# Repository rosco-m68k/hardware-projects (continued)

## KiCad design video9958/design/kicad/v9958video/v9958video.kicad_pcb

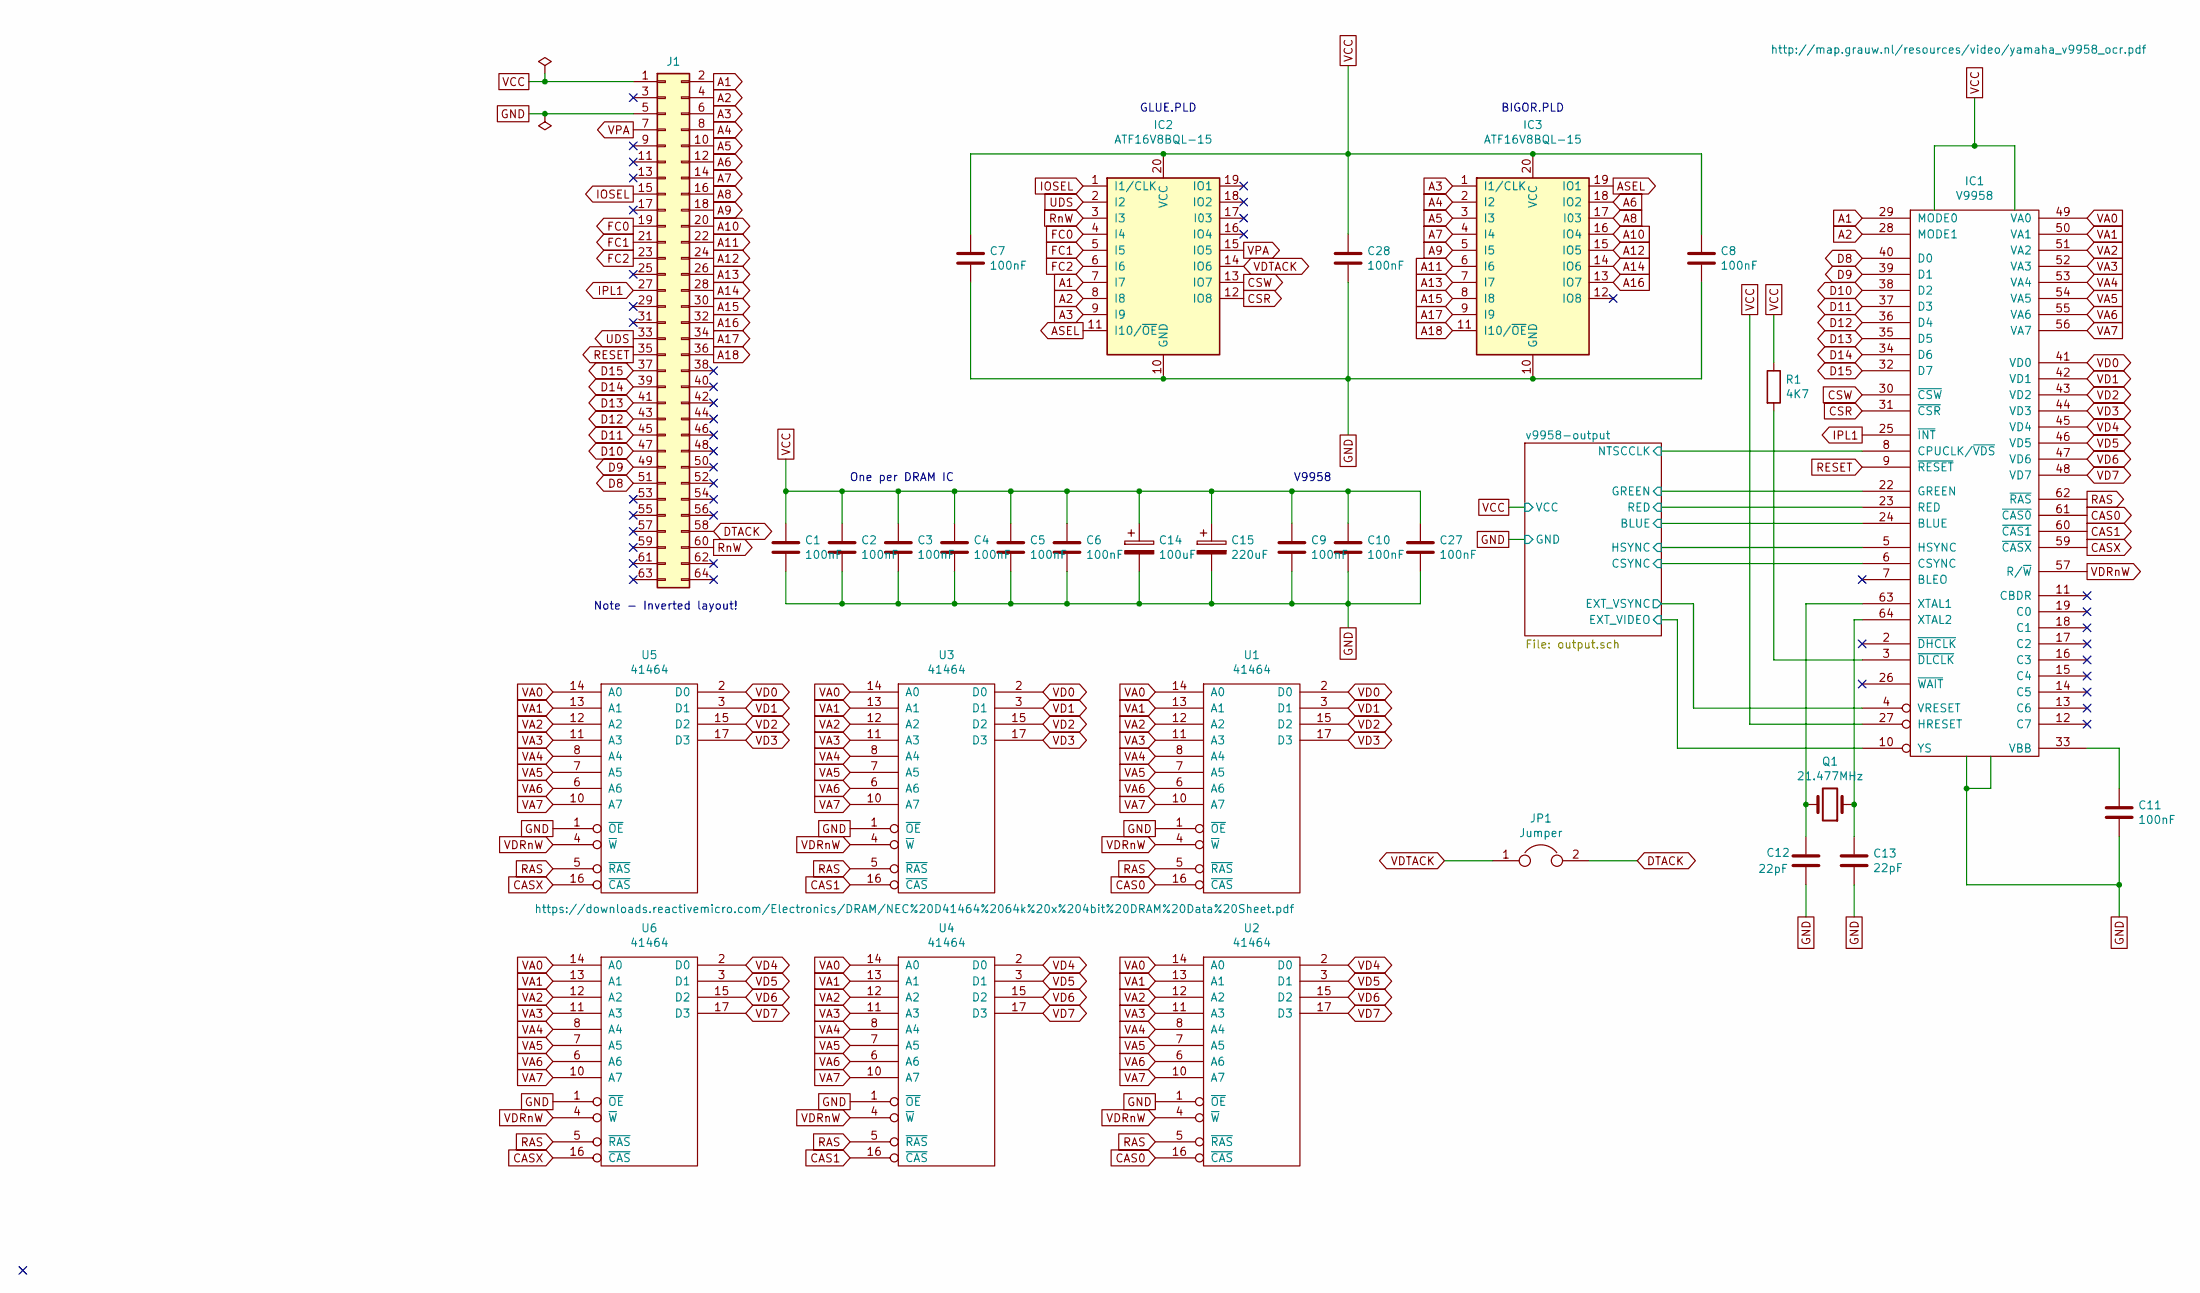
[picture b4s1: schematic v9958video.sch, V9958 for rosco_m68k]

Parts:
C1, C2, C3, C4, C5, C6, C7, C8, C9, C10, C11, C27, C28: 100nF; C_Rect_L7.0mm_W2.5mm_P5.00mm
C12, C13: 22pF; C_Rect_L7.0mm_W2.5mm_P5.00mm
C14: 100uF; CP_Radial_D5.0mm_P2.50mm
C15: 220uF; CP_Radial_D6.3mm_P2.50mm
IC1: V9958; sdip64
IC2, IC3: ATF16V8BQL-15; DIP-20_W7.62mm_LongPads
J1: Conn_02x32_Odd_Even; pin-2X32
JP1: Jumper; pin-1X02
Q1: 21.477MHz; HC49_S
R1: 4K7; R-0207_10
U1, U2, U3, U4, U5, U6: 41464; DIP-18_W7.62mm_Socket_LongPads

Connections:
/v9958-output/BLUE: IC1.24 (BLUE); also elsewhere on the board
/v9958-output/CSYNC: IC1.6 (CSYNC); also elsewhere on the board
/v9958-output/EXT_VIDEO: IC1.10 (YS); also elsewhere on the board
/v9958-output/EXT_VSYNC: IC1.4 (VRESET); also elsewhere on the board
/v9958-output/GREEN: IC1.22 (GREEN); also elsewhere on the board
/v9958-output/HSYNC: IC1.5 (HSYNC); also elsewhere on the board
/v9958-output/NTSCCLK: IC1.8 (CPUCLK/~VDS); also elsewhere on the board
/v9958-output/RED: IC1.23 (RED); also elsewhere on the board
A1: IC1.29 (MODE0), IC2.7 (I7), J1.2
A2: IC1.28 (MODE1), IC2.8 (I8), J1.4
A3: IC2.9 (I9), IC3.1 (I1/CLK), J1.6
A4: IC3.2 (I2), J1.8
A5: IC3.3 (I3), J1.10
A6: IC3.18 (IO2), J1.12
A7: IC3.4 (I4), J1.14
A8: IC3.17 (I03), J1.16
A9: IC3.5 (I5), J1.18
A10: IC3.16 (IO4), J1.20
A11: IC3.6 (I6), J1.22
A12: IC3.15 (IO5), J1.24
A13: IC3.7 (I7), J1.26
A14: IC3.14 (IO6), J1.28
A15: IC3.8 (I8), J1.30
A16: IC3.13 (IO7), J1.32
A17: IC3.9 (I9), J1.34
A18: IC3.11 (I10/~OE~), J1.36
ASEL: IC2.11 (I10/~OE~), IC3.19 (IO1)
CAS0: IC1.61 (~CAS0), U1.16 (~CAS), U2.16 (~CAS)
CAS1: IC1.60 (~CAS1), U3.16 (~CAS), U4.16 (~CAS)
CASX: IC1.59 (~CASX), U5.16 (~CAS), U6.16 (~CAS)
CSR: IC1.31 (~CSR), IC2.12 (IO8)
CSW: IC1.30 (~CSW), IC2.13 (IO7)
D8: IC1.40 (D0), J1.51
D9: IC1.39 (D1), J1.49
D10: IC1.38 (D2), J1.47
D11: IC1.37 (D3), J1.45
D12: IC1.36 (D4), J1.43
D13: IC1.35 (D5), J1.41
D14: IC1.34 (D6), J1.39
D15: IC1.32 (D7), J1.37
DTACK: J1.58, JP1.2
FC0: IC2.4 (I4), J1.19
FC1: IC2.5 (I5), J1.21
FC2: IC2.6 (I6), J1.23
IOSEL: IC2.1 (I1/CLK), J1.15
IPL1: IC1.25 (~INT), J1.27
unnamed: C11.1, IC1.33 (VBB)
unnamed: C12.1, IC1.63 (XTAL1), Q1.2
unnamed: C13.1, IC1.64 (XTAL2), Q1.1
unnamed: IC1.3 (~DLCLK), R1.2
RAS: IC1.62 (~RAS), U1.5 (~RAS), U2.5 (~RAS), U3.5 (~RAS), U4.5 (~RAS), U5.5 (~RAS), U6.5 (~RAS)
RESET: IC1.9 (~RESET), J1.35
RnW: IC2.3 (I3), J1.60
UDS: IC2.2 (I2), J1.33
VA0: IC1.49 (VA0), U1.14 (A0), U2.14 (A0), U3.14 (A0), U4.14 (A0), U5.14 (A0), U6.14 (A0)
VA1: IC1.50 (VA1), U1.13 (A1), U2.13 (A1), U3.13 (A1), U4.13 (A1), U5.13 (A1), U6.13 (A1)
VA2: IC1.51 (VA2), U1.12 (A2), U2.12 (A2), U3.12 (A2), U4.12 (A2), U5.12 (A2), U6.12 (A2)
VA3: IC1.52 (VA3), U1.11 (A3), U2.11 (A3), U3.11 (A3), U4.11 (A3), U5.11 (A3), U6.11 (A3)
VA4: IC1.53 (VA4), U1.8 (A4), U2.8 (A4), U3.8 (A4), U4.8 (A4), U5.8 (A4), U6.8 (A4)
VA5: IC1.54 (VA5), U1.7 (A5), U2.7 (A5), U3.7 (A5), U4.7 (A5), U5.7 (A5), U6.7 (A5)
VA6: IC1.55 (VA6), U1.6 (A6), U2.6 (A6), U3.6 (A6), U4.6 (A6), U5.6 (A6), U6.6 (A6)
VA7: IC1.56 (VA7), U1.10 (A7), U2.10 (A7), U3.10 (A7), U4.10 (A7), U5.10 (A7), U6.10 (A7)
VD0: IC1.41 (VD0), U1.2 (D0), U3.2 (D0), U5.2 (D0)
VD1: IC1.42 (VD1), U1.3 (D1), U3.3 (D1), U5.3 (D1)
VD2: IC1.43 (VD2), U1.15 (D2), U3.15 (D2), U5.15 (D2)
VD3: IC1.44 (VD3), U1.17 (D3), U3.17 (D3), U5.17 (D3)
VD4: IC1.45 (VD4), U2.2 (D0), U4.2 (D0), U6.2 (D0)
VD5: IC1.46 (VD5), U2.3 (D1), U4.3 (D1), U6.3 (D1)
VD6: IC1.47 (VD6), U2.15 (D2), U4.15 (D2), U6.15 (D2)
VD7: IC1.48 (VD7), U2.17 (D3), U4.17 (D3), U6.17 (D3)
VDRnW: IC1.57 (R/~W), U1.4 (~W), U2.4 (~W), U3.4 (~W), U4.4 (~W), U5.4 (~W), U6.4 (~W)
VDTACK: IC2.14 (IO6), JP1.1
VPA: IC2.15 (IO5), J1.7

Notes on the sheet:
GLUE.PLD
BIGOR.PLD
Note - Inverted layout!
One per DRAM IC
V9958

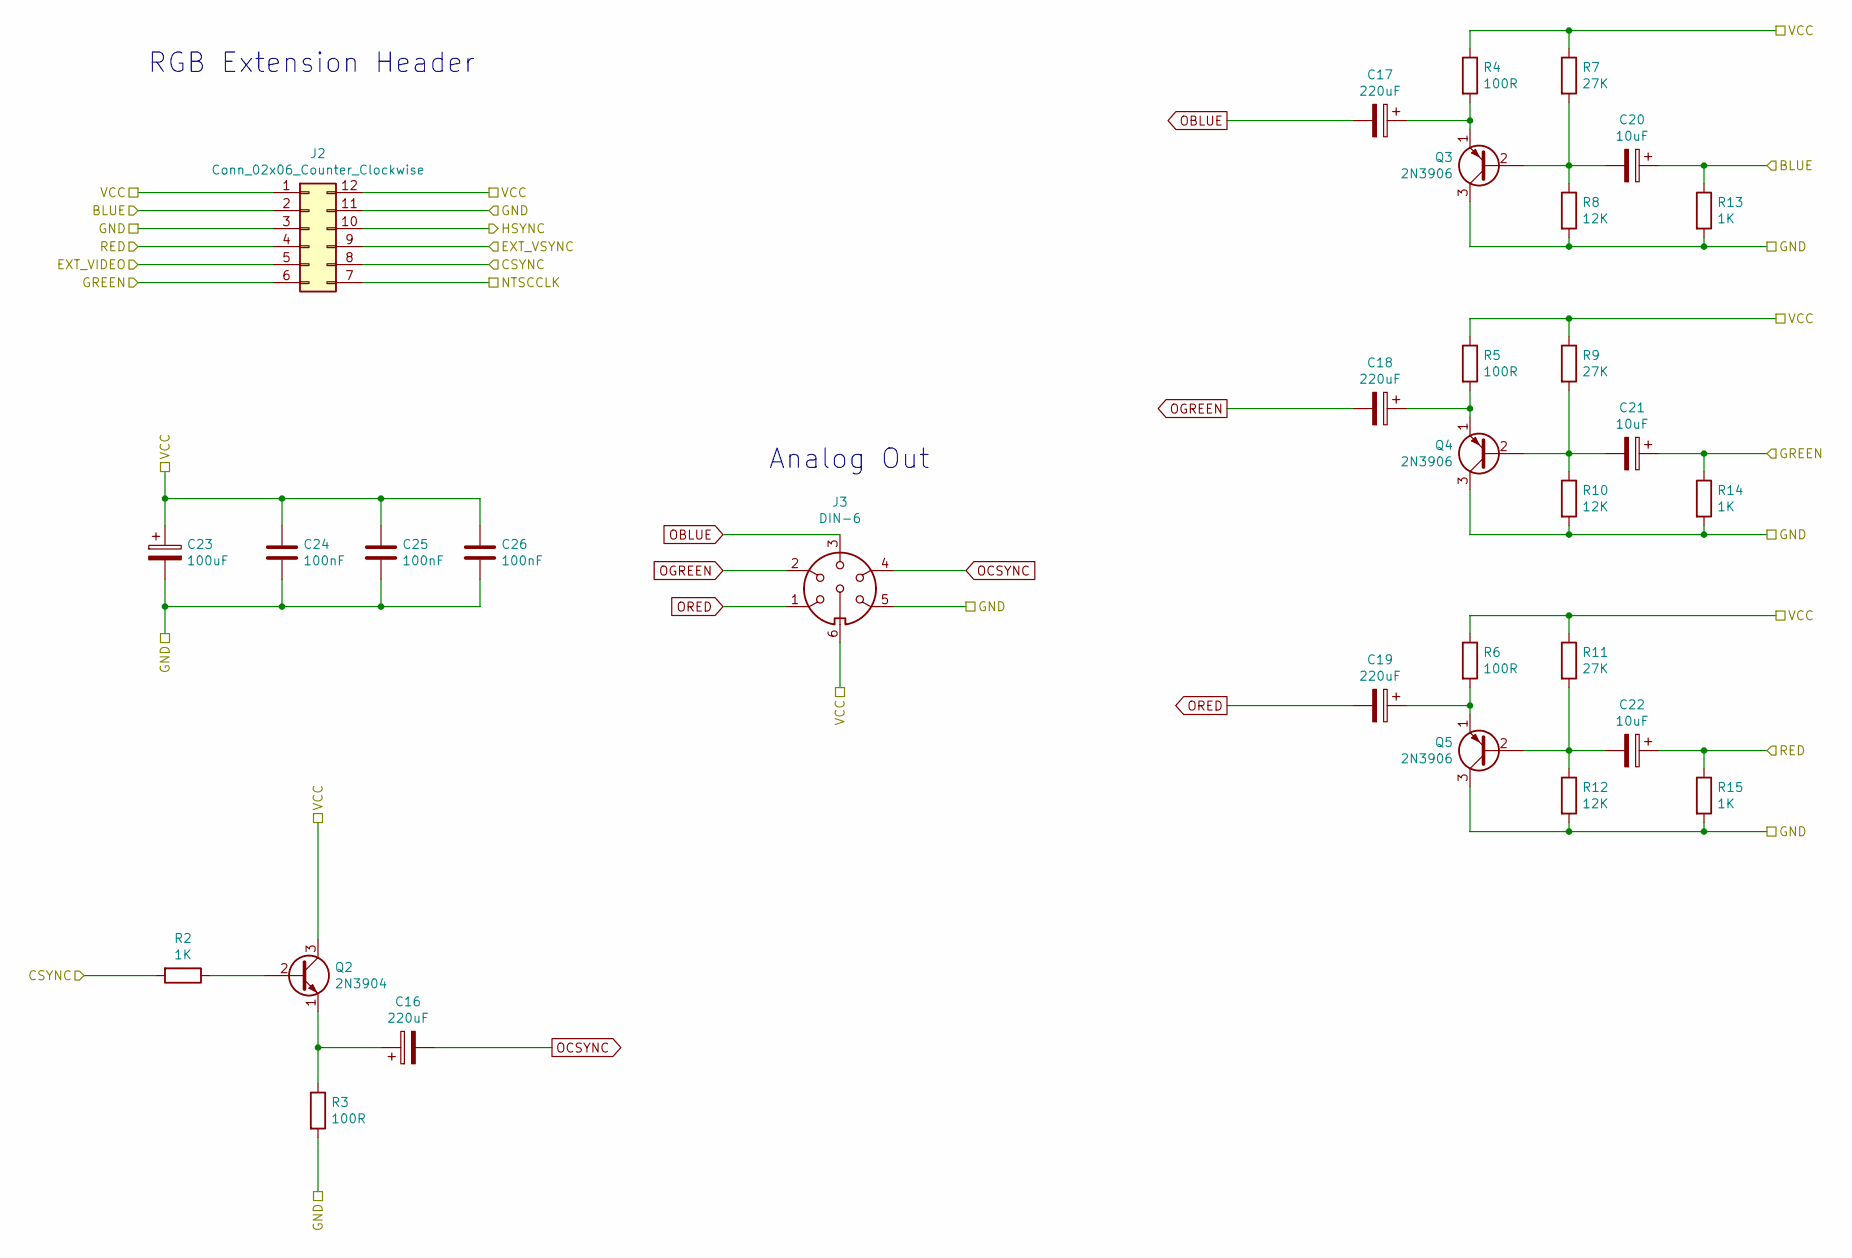
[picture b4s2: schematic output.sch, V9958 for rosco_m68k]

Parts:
C16, C17, C18, C19: 220uF; CP_Radial_D6.3mm_P2.50mm
C20, C21, C22: 10uF; CP_Radial_D5.0mm_P2.50mm
C23: 100uF; CP_Radial_D5.0mm_P2.50mm
C24, C25, C26: 100nF; C_Rect_L7.0mm_W2.5mm_P5.00mm
J2: Conn_02x06_Counter_Clockwise; PinHeader_2x06_P2.54mm_Vertical
J3: DIN-6; din-6
Q2: 2N3904; TO-92_Inline
Q3, Q4, Q5: 2N3906; TO-92_Inline
R2, R13, R14, R15: 1K; R-0207_10
R3, R4, R5, R6: 100R; R-0207_10
R7, R9, R11: 27K; R-0207_10
R8, R10, R12: 12K; R-0207_10

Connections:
/v9958-output/BLUE: C20.1, J2.2, R13.1; also elsewhere on the board
/v9958-output/CSYNC: J2.8, R2.2; also elsewhere on the board
/v9958-output/EXT_VIDEO: J2.5; also elsewhere on the board
/v9958-output/EXT_VSYNC: J2.9; also elsewhere on the board
/v9958-output/GREEN: C21.1, J2.6, R14.1; also elsewhere on the board
/v9958-output/HSYNC: J2.10; also elsewhere on the board
/v9958-output/NTSCCLK: J2.7; also elsewhere on the board
/v9958-output/RED: C22.1, J2.4, R15.1; also elsewhere on the board
unnamed: C16.1, Q2.1 (E), R3.1
unnamed: C17.1, Q3.1 (E), R4.2
unnamed: C18.1, Q4.1 (E), R5.2
unnamed: C19.1, Q5.1 (E), R6.2
unnamed: C20.2, Q3.2 (B), R7.2, R8.1
unnamed: C21.2, Q4.2 (B), R9.2, R10.1
unnamed: C22.2, Q5.2 (B), R11.2, R12.1
unnamed: Q2.2 (B), R2.1
OBLUE: C17.2, J3.3
OCSYNC: C16.2, J3.4
OGREEN: C18.2, J3.2
ORED: C19.2, J3.1

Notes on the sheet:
Analog Out
RGB Extension Header

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
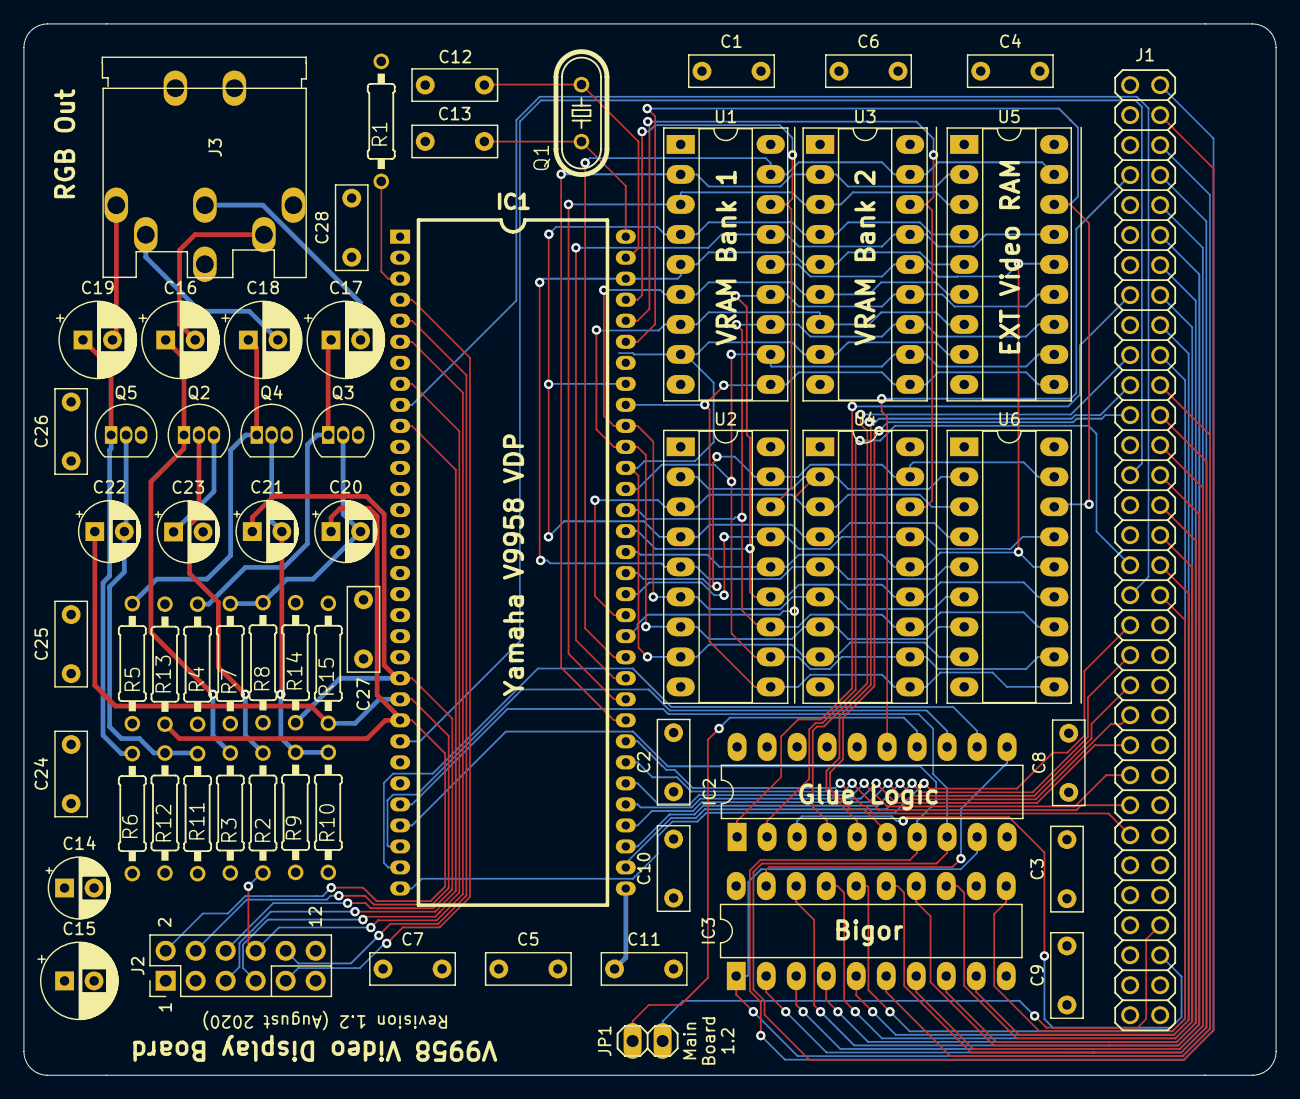
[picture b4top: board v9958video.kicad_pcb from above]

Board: 4 copper layers, 106.0 x 89.0 mm, 61 parts (0 on the bottom side), 87 nets.
